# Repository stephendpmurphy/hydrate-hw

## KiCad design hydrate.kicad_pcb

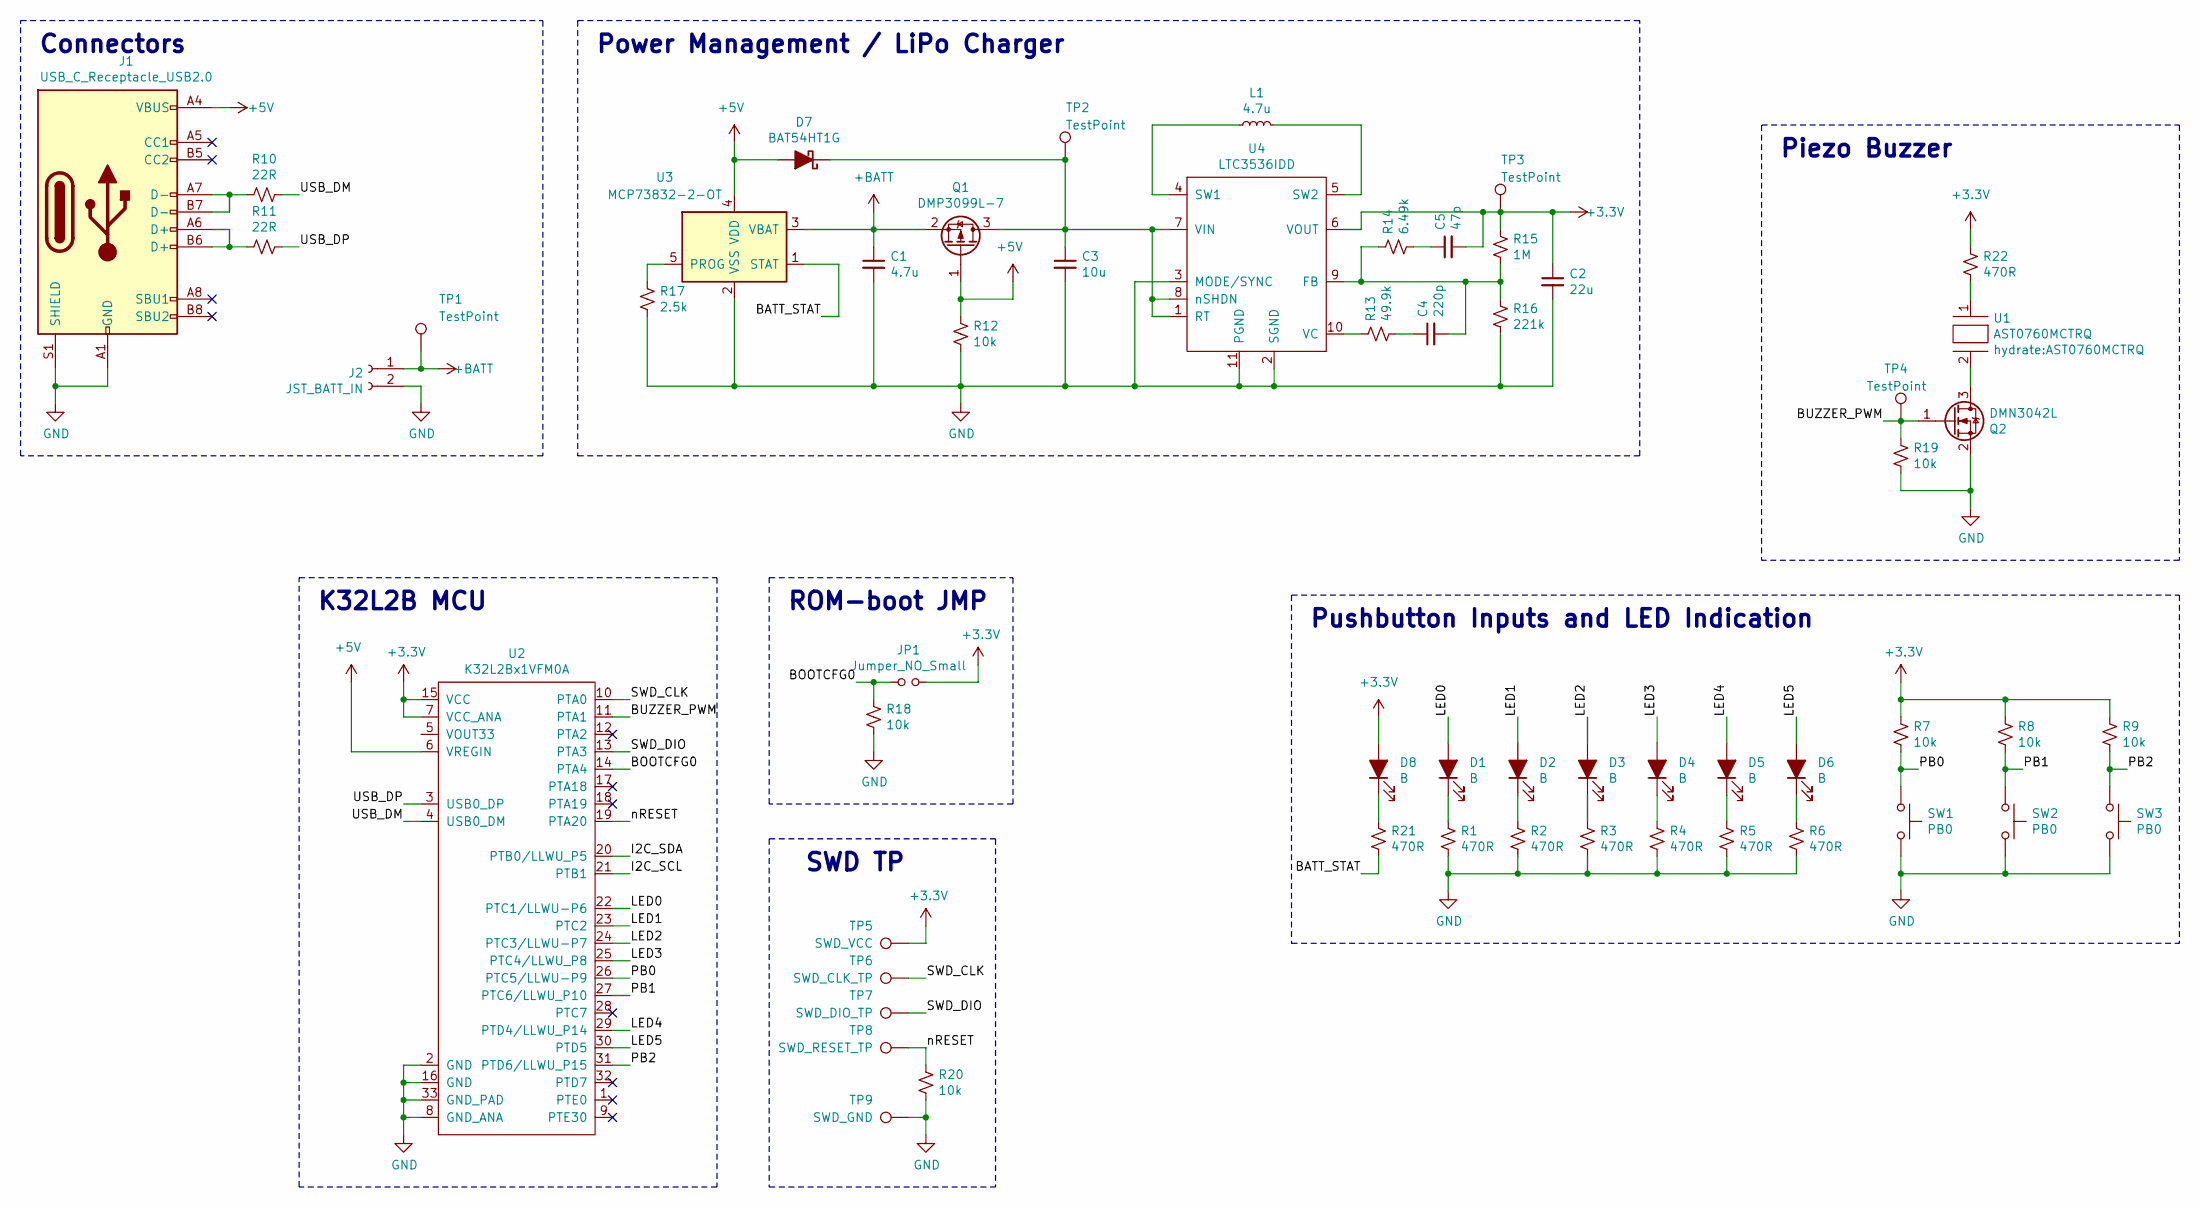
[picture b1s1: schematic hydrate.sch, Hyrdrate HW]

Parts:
C1: 4.7u; C_0402_1005Metric
C2: 22u; C_0402_1005Metric
C3: 10u; C_0402_1005Metric
C4: 220p; C_0402_1005Metric
C5: 47p; C_0402_1005Metric
D1, D2, D3, D4, D5, D6, D8: B; LED_0402_1005Metric
D7: BAT54HT1G; D_SOD-323
J1: USB_C_Receptacle_USB2.0; USB_C_Receptacle_GCT_USB4085
J2: JST_BATT_IN; JST_PH_S2B-PH-SM4-TB_1x02-1MP_P2.00mm_Horizontal
JP1: Jumper_NO_Small; SolderJumper-2_P1.3mm_Open_TrianglePad1.0x1.5mm
L1: 4.7u; C_0402_1005Metric
Q1: DMP3099L-7; SOT-23
Q2: DMN3042L; SOT-23
R1, R2, R3, R4, R5, R6, R21, R22: 470R; R_0402_1005Metric
R7, R8, R9, R12, R18, R19, R20: 10k; R_0402_1005Metric
R10, R11: 22R; R_0402_1005Metric
R13: 49.9k; R_0402_1005Metric
R14: 6.49k; R_0402_1005Metric
R15: 1M; R_0402_1005Metric
R16: 221k; R_0402_1005Metric
R17: 2.5k; R_0402_1005Metric
SW1, SW2, SW3: PB0; Panasonic_EVQPUK_EVQPUB
TP1, TP2, TP3, TP4: TestPoint; TestPoint_Pad_1.0x1.0mm
TP5: SWD_VCC; TestPoint_Pad_1.5x1.5mm
TP6: SWD_CLK_TP; TestPoint_Pad_1.5x1.5mm
TP7: SWD_DIO_TP; TestPoint_Pad_1.5x1.5mm
TP8: SWD_RESET_TP; TestPoint_Pad_1.5x1.5mm
TP9: SWD_GND; TestPoint_Pad_1.5x1.5mm
U1: AST0760MCTRQ
U2: K32L2Bx1VFM0A; QFN-32-1EP_5x5mm_P0.5mm_EP3.65x3.65mm
U3: MCP73832-2-OT; SOT-23-5
U4: LTC3536IDD; DFN-10-1EP_3x3mm_P0.5mm_EP1.65x2.38mm

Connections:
+3V3: C2.1, C5.2, D8.2 (A), JP1.2, R7.1, R8.1, R9.1, R15.1, R22.1, TP3.1, TP5.1, U2.7 (VCC_ANA), U2.15 (VCC), U4.6 (VOUT)
+5V: D7.2 (A), J1.A4 (VBUS), J1.A9 (VBUS), J1.B4 (VBUS), J1.B9 (VBUS), Q1.1 (G), R12.1, U2.6 (VREGIN), U3.4 (VDD)
+BATT: C1.1, J2.1, Q1.2 (S), TP1.1, U3.3 (VBAT)
/BATT_STAT: R21.2, U3.1 (STAT)
/BOOTCFG0: JP1.1, R18.1, U2.14 (PTA4)
/BUZZER_PWM: Q2.1 (G), R19.1, TP4.1, U2.11 (PTA1)
/I2C_SCL: U2.21 (PTB1)
/I2C_SDA: U2.20 (PTB0/LLWU_P5)
/LED0: D1.2 (A), U2.22 (PTC1/LLWU-P6)
/LED1: D2.2 (A), U2.23 (PTC2)
/LED2: D3.2 (A), U2.24 (PTC3/LLWU-P7)
/LED3: D4.2 (A), U2.25 (PTC4/LLWU_P8)
/LED4: D5.2 (A), U2.29 (PTD4/LLWU_P14)
/LED5: D6.2 (A), U2.30 (PTD5)
/PB0: R7.2, SW1.1, U2.26 (PTC5/LLWU-P9)
/PB1: R8.2, SW2.1, U2.27 (PTC6/LLWU_P10)
/PB2: R9.2, SW3.1, U2.31 (PTD6/LLWU_P15)
/SWD_CLK: TP6.1, U2.10 (PTA0)
/SWD_DIO: TP7.1, U2.13 (PTA3)
/USB_DM: R10.1, U2.4 (USB0_DM)
/USB_DP: R11.1, U2.3 (USB0_DP)
/nRESET: R20.1, TP8.1, U2.19 (PTA20)
GND: C1.2, C2.2, C3.2, J1.A1 (GND), J1.A12 (GND), J1.B1 (GND), J1.B12 (GND), J1.S1 (SHIELD), J2.2, Q2.2 (S), R1.2, R2.2, R3.2, R4.2, R5.2, R6.2, R12.2, R16.2, R17.2, R18.2, R19.2, R20.2, SW1.2, SW2.2, SW3.2, TP9.1, U2.2 (GND), U2.8 (GND_ANA), U2.16 (GND), U2.33 (GND_PAD), U3.2 (VSS), U4.2 (SGND), U4.3 (MODE/SYNC), U4.11 (PGND)
unnamed: C3.1, D7.1 (K), Q1.3 (D), TP2.1, U4.1 (RT), U4.7 (VIN), U4.8 (nSHDN)
unnamed: C4.1, R13.2
unnamed: C4.2, R14.1, R15.2, R16.1, U4.9 (FB)
unnamed: C5.1, R14.2
unnamed: D1.1 (K), R1.1
unnamed: D2.1 (K), R2.1
unnamed: D3.1 (K), R3.1
unnamed: D4.1 (K), R4.1
unnamed: D5.1 (K), R5.1
unnamed: D6.1 (K), R6.1
unnamed: D8.1 (K), R21.1
unnamed: J1.A6 (D+), J1.B6 (D+), R11.2
unnamed: J1.A7 (D-), J1.B7 (D-), R10.2
unnamed: L1.1, U4.4 (SW1)
unnamed: L1.2, U4.5 (SW2)
unnamed: Q2.3 (D), U1.2
unnamed: R13.1, U4.10 (VC)
unnamed: R17.1, U3.5 (PROG)
unnamed: R22.2, U1.1

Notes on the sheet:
Connectors
Pushbutton Inputs and LED Indication
Piezo Buzzer
Power Management / LiPo Charger
K32L2B MCU
SWD TP
ROM-boot JMP

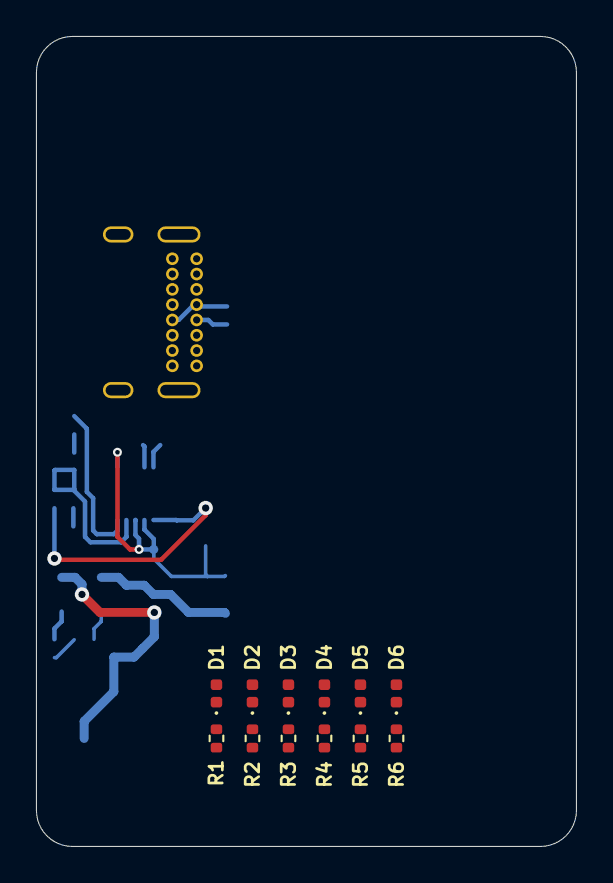
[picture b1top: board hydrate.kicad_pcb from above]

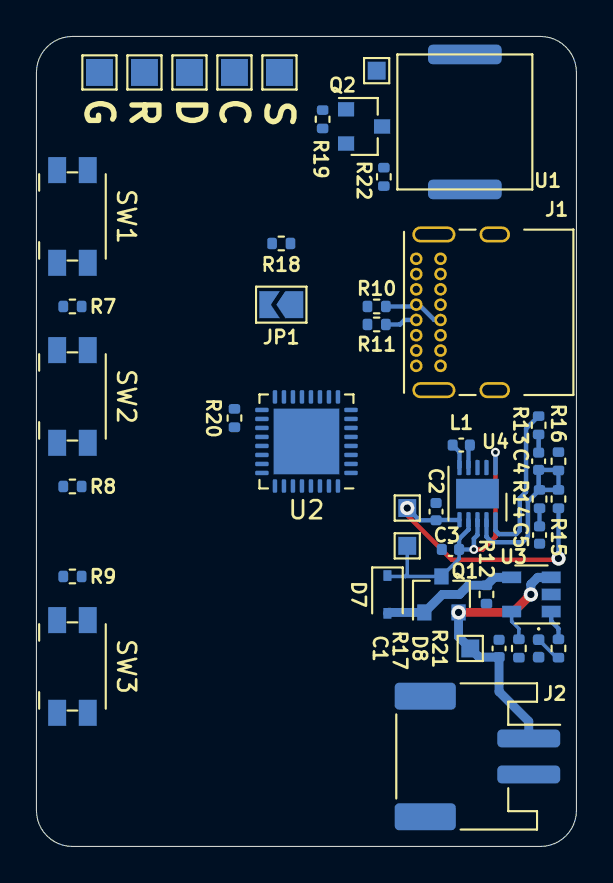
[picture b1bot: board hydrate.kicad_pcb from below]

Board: 2 copper layers, 30.0 x 45.0 mm, 57 parts (45 on the bottom side), 40 nets.

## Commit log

2021-11-15 Adding initial project and footprint for the K32L2B
2021-11-23 Saving place. MCU and power management ICs added
2021-11-29 Added LT switcher
2021-12-10 Began layout of Switcher and Battery charger on backside of board
2021-12-15 Moving to standard footprints and laying out bottom layer
